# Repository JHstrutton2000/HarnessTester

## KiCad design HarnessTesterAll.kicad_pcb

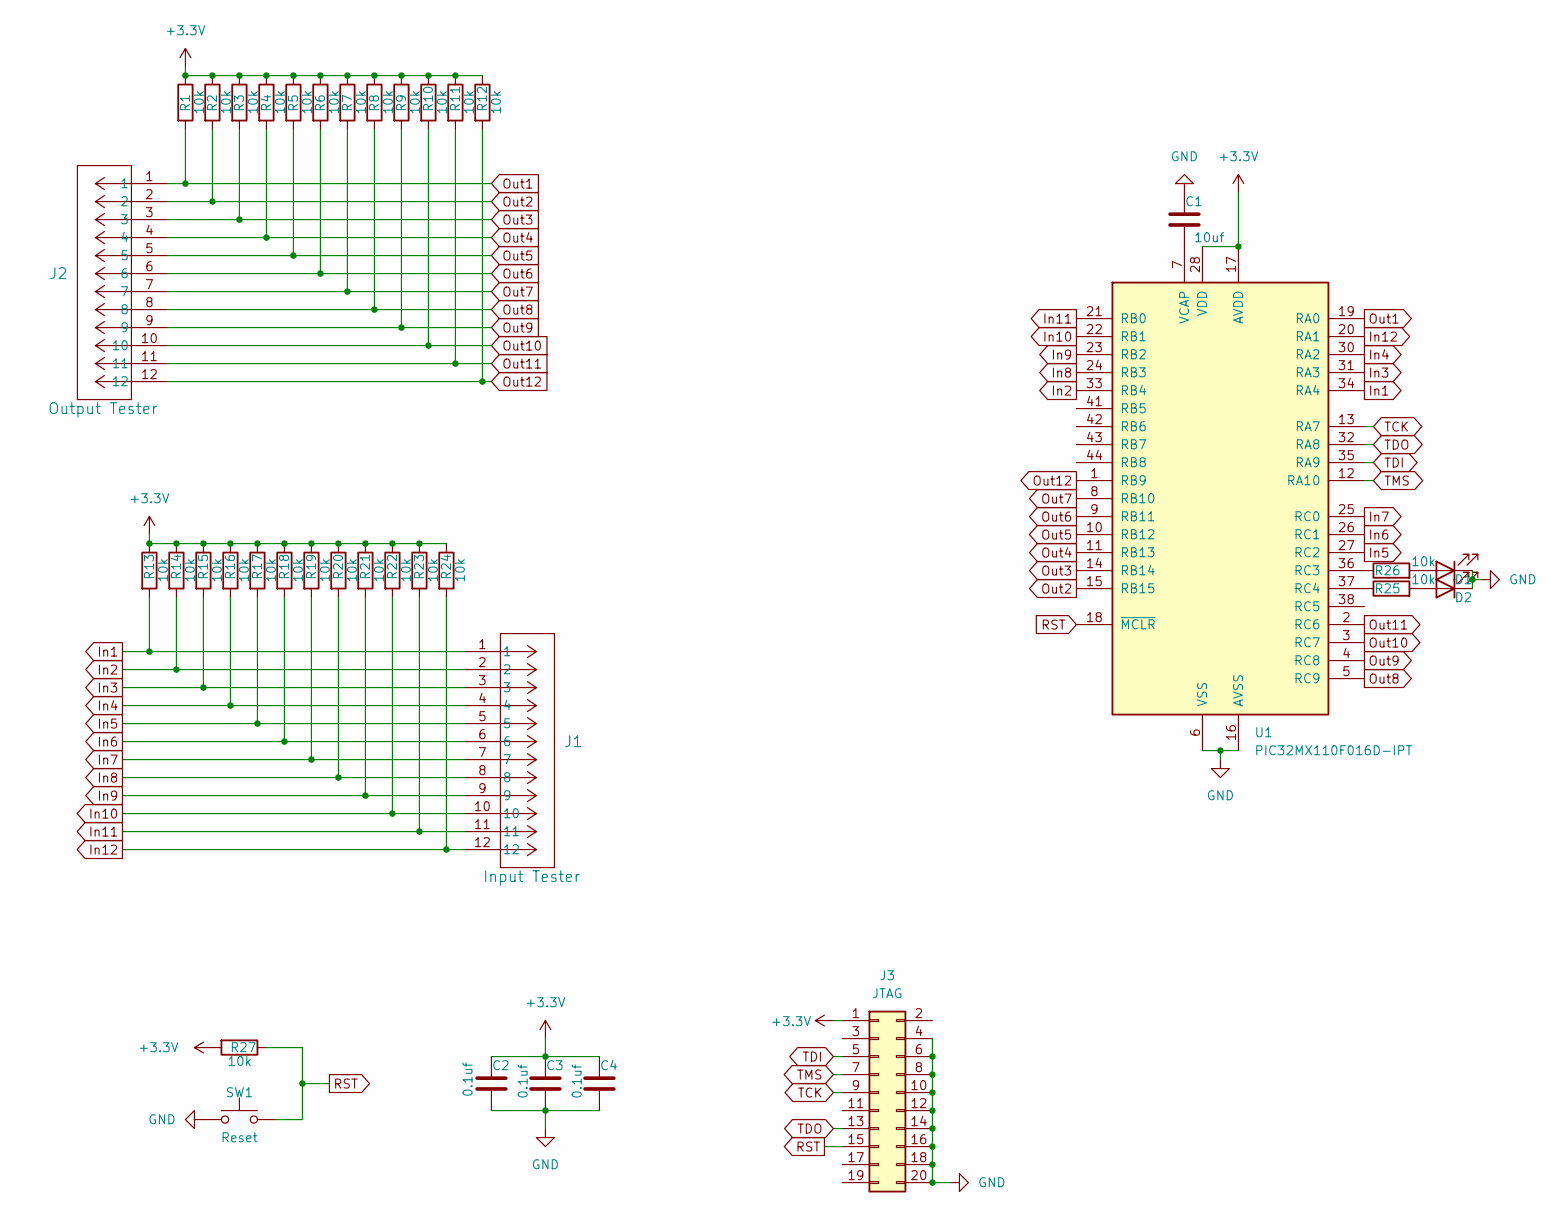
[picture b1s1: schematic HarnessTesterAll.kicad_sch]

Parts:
C1: 10uf; C_0603_1608Metric
C2, C3, C4: 0.1uf; C_0603_1608Metric
D1, D2: LED; LED_0603_1608Metric
J1: Input Tester; CON_874271202
J2: Output Tester; CON_874271202
J3: JTAG; PinHeader_2x10_P1.27mm_Vertical
R1, R2, R3, R4, R5, R6, R7, R8, R9, R10, R11, R12, R13, R14, R15, R16, R17, R18, R19, R20, R21, R22, R23, R24, R25, R26, R27: 10k; R_0603_1608Metric
SW1: Reset; SW_MEC_5GSH9
U1: PIC32MX110F016D-IPT; TQFP-44_10x10mm_P0.8mm

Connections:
+3.3V: C2.1, C3.1, C4.1, J3.1, R1.1, R2.1, R3.1, R4.1, R5.1, R6.1, R7.1, R8.1, R9.1, R10.1, R11.1, R12.1, R13.1, R14.1, R15.1, R16.1, R17.1, R18.1, R19.1, R20.1, R21.1, R22.1, R23.1, R24.1, R27.2, U1.17 (AVDD), U1.28 (VDD), U1.40 (VDD)
GND: C1.1, C2.2, C3.2, C4.2, D1.1 (K), D2.1 (K), J3.4, J3.6, J3.8, J3.10, J3.12, J3.14, J3.16, J3.18, J3.20, SW1.1, U1.6 (VSS), U1.16 (AVSS), U1.29 (VSS), U1.39 (VSS)
In1: J1.1, R13.2, U1.34 (RA4)
In2: J1.2, R14.2, U1.33 (RB4)
In3: J1.3, R15.2, U1.31 (RA3)
In4: J1.4, R16.2, U1.30 (RA2)
In5: J1.5, R17.2, U1.27 (RC2)
In6: J1.6, R18.2, U1.26 (RC1)
In7: J1.7, R19.2, U1.25 (RC0)
In8: J1.8, R20.2, U1.24 (RB3)
In9: J1.9, R21.2, U1.23 (RB2)
In10: J1.10, R22.2, U1.22 (RB1)
In11: J1.11, R23.2, U1.21 (RB0)
In12: J1.12, R24.2, U1.20 (RA1)
unnamed: D1.2 (A), R26.2
unnamed: D2.2 (A), R25.2
unnamed: R26.1, U1.36 (RC3)
unnamed: R25.1, U1.37 (RC4)
unnamed: C1.2, U1.7 (VCAP)
Out1: J2.1, R1.2, U1.19 (RA0)
Out2: J2.2, R2.2, U1.15 (RB15)
Out3: J2.3, R3.2, U1.14 (RB14)
Out4: J2.4, R4.2, U1.11 (RB13)
Out5: J2.5, R5.2, U1.10 (RB12)
Out6: J2.6, R6.2, U1.9 (RB11)
Out7: J2.7, R7.2, U1.8 (RB10)
Out8: J2.8, R8.2, U1.5 (RC9)
Out9: J2.9, R9.2, U1.4 (RC8)
Out10: J2.10, R10.2, U1.3 (RC7)
Out11: J2.11, R11.2, U1.2 (RC6)
Out12: J2.12, R12.2, U1.1 (RB9)
RST: J3.15, R27.1, SW1.2, U1.18 (~MCLR)
TCK: J3.9, U1.13 (RA7)
TDI: J3.5, U1.35 (RA9)
TDO: J3.13, U1.32 (RA8)
TMS: J3.7, U1.12 (RA10)

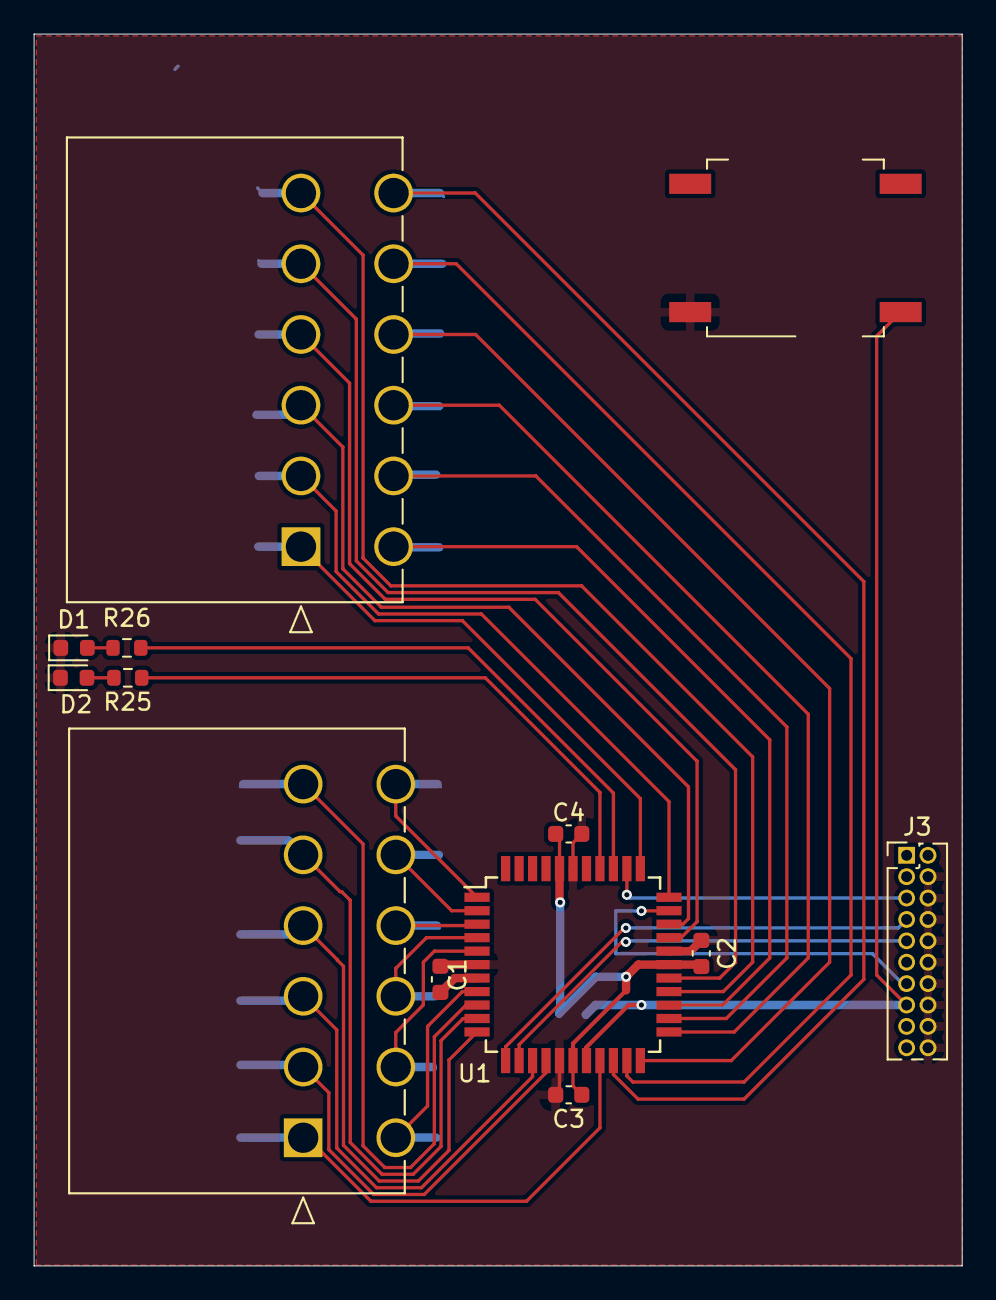
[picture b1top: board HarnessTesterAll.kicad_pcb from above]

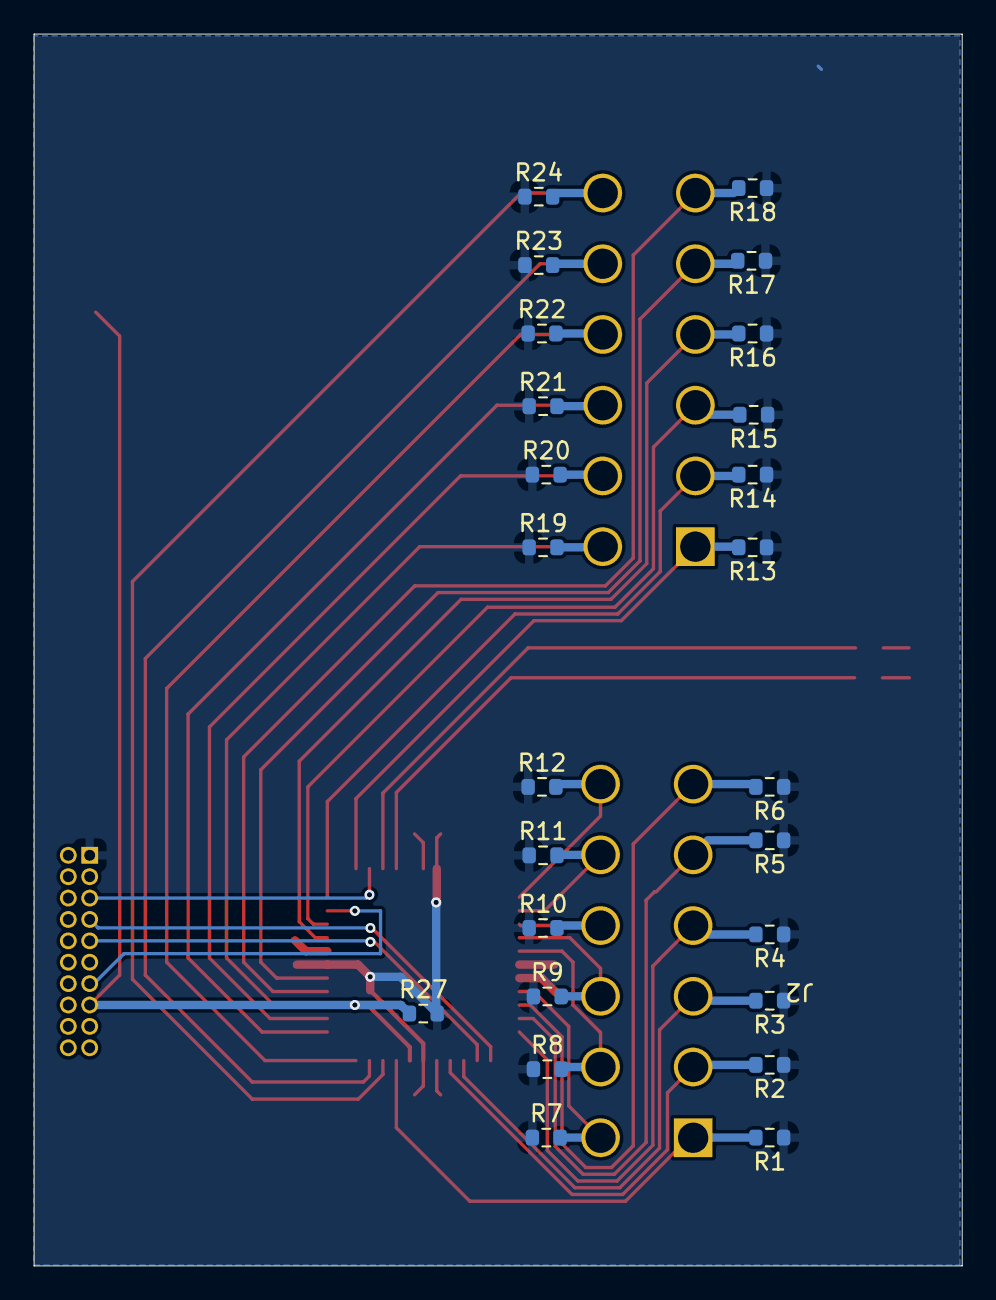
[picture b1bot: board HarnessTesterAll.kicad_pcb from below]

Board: 2 copper layers, 55.1 x 73.2 mm, 38 parts (25 on the bottom side), 36 nets.

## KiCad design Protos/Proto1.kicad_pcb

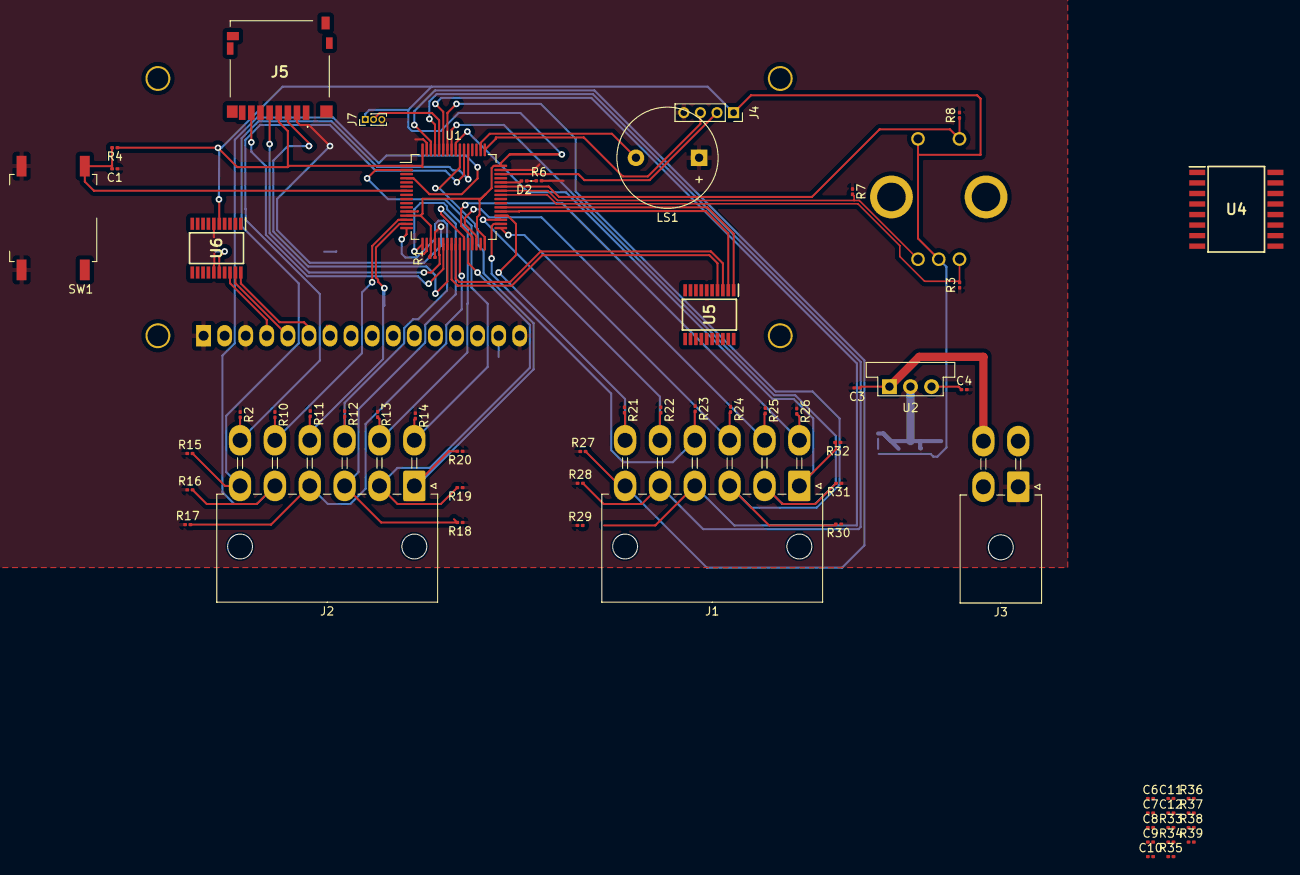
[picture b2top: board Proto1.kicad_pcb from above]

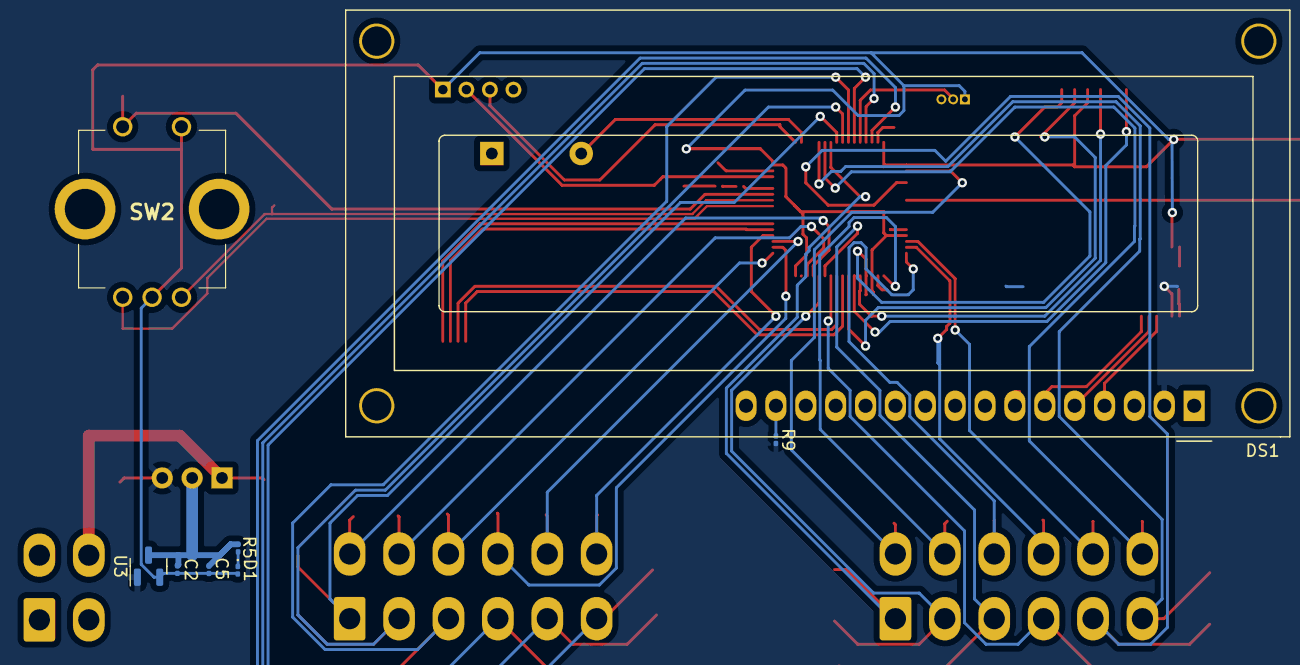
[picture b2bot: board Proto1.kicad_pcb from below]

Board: 2 copper layers, 69 parts (8 on the bottom side), 78 nets.

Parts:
C1, C2, C3, C4, C5, C11, C12: 0.1uf; R_0201_0603Metric
C6, C7, C8, C9, C10: 1uf; R_0201_0603Metric
D1, D2: LED; LED_0201_0603Metric
DS1: LCD; WC1602A
J1: I/O B; Molex_Mini-Fit_Jr_5569-12A2_2x06_P4.20mm_Horizontal
J2: I/O A; Molex_Mini-Fit_Jr_5569-12A2_2x06_P4.20mm_Horizontal
J3: Power; Molex_Mini-Fit_Jr_5569-04A2_2x02_P4.20mm_Horizontal
J4: SWD; PinSocket_1x04_P2.00mm_Vertical
J5: Micro_SD_Card; DM3DSF
J7: Boot; PinHeader_1x03_P1.00mm_Vertical
LS1: Speaker_Crystal; Buzzer_12x9.5RM7.6
R1, R2, R3, R4, R7, R8, R10, R11, R12, R13, R14, R15, R16, R17, R18, R19, R20, R21, R22, R23, R24, R25, R26, R27, R28, R29, R30, R31, R32, R33, R34, R35, R36, R37, R38, R39: 10k; R_0201_0603Metric
R5, R6, R9: 470; R_0201_0603Metric
SW1: SW_MEC_5G; SW_MEC_5GSH9
SW2: RoterySwitch; PEC11R4220FS0024
U1: STM32F103RETx; LQFP-64_10x10mm_P0.5mm
U2: 5v regulator; Converter_DCDC_Murata_OKI-78SR_Vertical
U3: 3.3v Regulator; SOT-23
U4: MAX232; SOIC127P1032X265-16N
U5, U6: TXB0108; SOP65P640X120-20N

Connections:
232In1: J3.2, U4.13 (R1IN)
232Out1: J3.3, U4.14 (T1OUT)
+3.3V: C2.1, C5.1, C12.1, D1.2 (A), J4.1, J5.4 (VDD), J7.1, R4.1, R37.1, SW2.2, SW2.C1 (C), U1.1 (VBAT), U1.13 (VDDA), U1.19 (VDD), U1.32 (VDD), U1.48 (VDD), U1.64 (VDD), U3.2 (VO), U5.5 (VCCA), U6.5 (VCCA)
+5V: C4.1, C10.1, C11.1, DS1.2 (VDD), R9.2, R33.1, R34.1, R35.1, R36.1, U2.3 (OUT), U3.1 (VI), U4.16 (VCC), U5.16 (VCCB), U6.16 (VCCB)
+12V: C3.1, J3.4, U2.1 (IN)
Boot0: J7.2, U1.60 (BOOT0)
Button: R1.2, R8.1, SW2.1, U1.43 (PA10)
EA: U1.40 (PC9), U6.1 (A1)
EB: DS1.6 (E), U6.20 (B1)
Enc+: R3.2, R39.2, SW2.A1 (A), U1.41 (PA8)
Enc-: R7.2, R38.2, SW2.B1 (B), U1.42 (PA9)
GND: C1.1, C2.2, C3.2, C4.2, C5.2, C8.1, C9.1, C10.2, C11.2, C12.2, DS1.1 (VSS), DS1.3 (VO), DS1.16 (LED(-)), J3.1, J4.4, J5.6 (VSS), J7.3, LS1.1, R1.1, R2.1, R3.1, R5.2, R6.2, R7.1, R8.2, R10.1, R11.1, R12.1, R13.1, R14.1, R15.1, R16.1, R17.1, R18.1, R19.1, R20.1, R21.1, R22.1, R23.1, R24.1, R25.1, R26.1, R27.1, R28.1, R29.1, R30.1, R31.1, R32.1, R38.1, R39.1, SW1.3 (B), SW1.4 (B), U1.12 (VSSA), U1.18 (VSS), U1.31 (VSS), U1.47 (VSS), U1.63 (VSS), U2.2 (GND), U3.3 (GND), U4.15 (GND), U5.6 (OE), U5.15 (GND), U6.6 (OE), U6.15 (GND)
HeartBeat: D2.2 (A), U1.44 (PA11)
In1: J1.1, R32.2, U1.56 (PB4)
In2: J1.2, R31.2, U1.57 (PB5)
In3: J1.3, R30.2, U1.58 (PB6)
In4: J1.4, R29.2, U1.59 (PB7)
In5: J1.5, R28.2, U1.61 (PB8)
In6: J1.6, R27.2, U1.62 (PB9)
In7: J1.7, R26.2, U1.29 (PB10)
In8: J1.8, R25.2, U1.30 (PB11)
In9: J1.9, R24.2, U1.33 (PB12)
In10: J1.10, R23.2, U1.34 (PB13)
In11: J1.11, R22.2, U1.35 (PB14)
In12: J1.12, R21.2, U1.36 (PB15)
unnamed: D1.1 (K), R5.1
unnamed: D2.1 (K), R6.1
unnamed: DS1.7 (D0), U5.11 (B8)
unnamed: DS1.8 (D1), U5.12 (B7)
unnamed: DS1.9 (D2), U5.13 (B6)
unnamed: DS1.10 (D3), U5.14 (B5)
unnamed: DS1.11 (D4), U5.17 (B4)
unnamed: DS1.12 (D5), U5.18 (B3)
unnamed: DS1.13 (D6), U5.19 (B2)
unnamed: DS1.14 (D7), U5.20 (B1)
unnamed: DS1.15 (LED(+)), R9.1
unnamed: J4.2, U1.46 (PA13)
unnamed: J4.3, U1.49 (PA14)
unnamed: J5.5 (CLK), U1.21 (PA5)
unnamed: J5.3 (CMD), U1.23 (PA7)
unnamed: J5.7 (DAT0), U1.22 (PA6)
unnamed: C1.2, R4.2, SW1.1 (A), SW1.2 (A), U1.7 (NRST)
unnamed: LS1.2, U1.50 (PA15)
unnamed: U1.8 (PC0), U5.10 (A8)
unnamed: U1.9 (PC1), U5.9 (A7)
unnamed: U1.10 (PC2), U5.8 (A6)
unnamed: U1.11 (PC3), U5.7 (A5)
unnamed: U1.24 (PC4), U5.4 (A4)
unnamed: U1.25 (PC5), U5.3 (A3)
unnamed: U1.37 (PC6), U5.2 (A2)
unnamed: U1.38 (PC7), U5.1 (A1)
unnamed: C7.1, U4.1 (C1+)
unnamed: C7.2, U4.3 (C1-)
unnamed: C6.1, U4.4 (C2+)
unnamed: C6.2, U4.5 (C2-)
unnamed: C9.2, U4.2 (VS+)
unnamed: C8.2, U4.6 (VS-)
Out1: J2.1, R20.2, U1.55 (PB3)
Out2: J2.2, R19.2, U1.28 (PB2)
Out3: J2.3, R18.2, U1.27 (PB1)
Out4: J2.4, R17.2, U1.26 (PB0)
Out5: J2.5, R16.2, U1.4 (PC15)
Out6: J2.6, R15.2, U1.53 (PC12)
Out7: J2.7, R14.2, U1.2 (PC13)
Out8: J2.8, R13.2, U1.17 (PA3)
Out9: J2.9, R12.2, U1.16 (PA2)
Out10: J2.10, R11.2, U1.15 (PA1)
Out11: J2.11, R10.2, U1.14 (PA0)
Out12: J2.12, R2.2, U1.54 (PD2)
R1OutA: U1.52 (PC11), U6.4 (A4)
R1OutB: U4.12 (R1OUT), U6.17 (B4)
RSA: U1.39 (PC8), U6.3 (A3)
RSB: DS1.4 (RS), U6.18 (B3)
T1InA: U1.51 (PC10), U6.7 (A5)
T1InB: U4.11 (T1IN), U6.14 (B5)
cs1: J5.2 (DAT3/CD), R37.2, U1.20 (PA4)
rwA: U1.3 (PC14), U6.2 (A2)
rwB: DS1.5 (R/W), U6.19 (B2)

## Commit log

2023-11-09 commited HarnessTester
2024-02-20 Started from scratch, Finished new schematic
2024-02-20 Made a board laylout
2024-02-20 Added more clearense and moved pull up resistors
2024-02-20 Added more clearense
2024-02-21 Added board outline
